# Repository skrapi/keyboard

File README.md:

# keyboard
Documenting my mechanical keyboard build

1. Put feet on case
1. Cut foam for M2 chip
1. Placed M2 Chip in keyboard
1. Plugged in computer
1. Flashing blue light on "1" key
1. Spacebar works
1. https://www.youtube.com/watch?v=usNx1_d0HbQ&t=84s
1. https://www.youtube.com/watch?v=cD5Zj-ZgMLA
1. Decided just to clip stabs, since I don't have lube
1. Mounted stabs with plastic washers
1. connected bluetooth and nfc antennas
1. Make sure that thehy are not in the way of the pcb mounting and switch connection holes
1. Cut case if needed to fit M2 boarD
1. Tested with online keyboard tester
1. Placed all the keycaps

## Designing keyboard
https://github.com/ruiqimao/keyboard-pcb-guide

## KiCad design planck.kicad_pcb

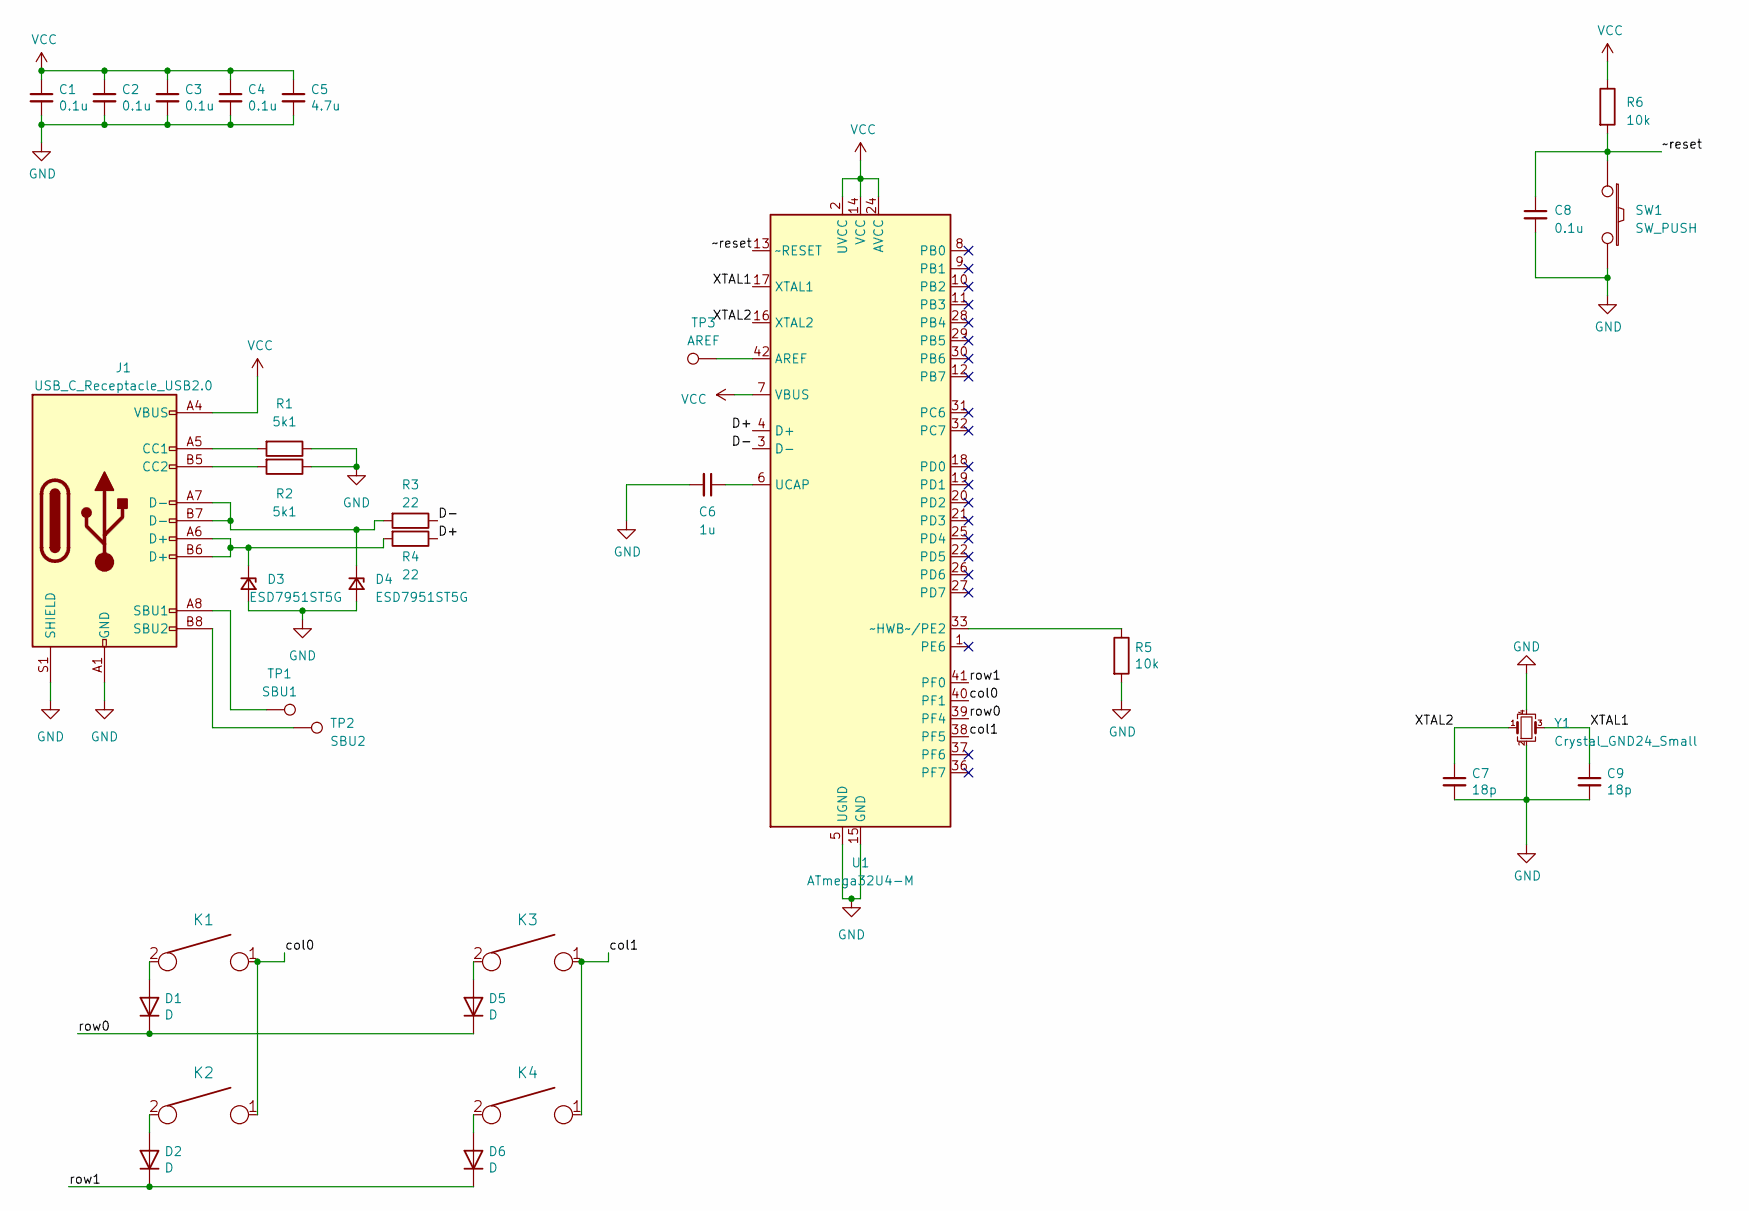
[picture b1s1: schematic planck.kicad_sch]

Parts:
C1, C2, C3, C4, C8: 0.1u; C_0402_1005Metric
C5: 4.7u; C_0402_1005Metric
C6: 1u; C_0402_1005Metric
C7, C9: 18p; C_0402_1005Metric
D1, D2, D5, D6: D; D_SOD-123
D3, D4: ESD7951ST5G; D_SOD-923
J1: USB_C_Receptacle_USB2.0; USB_C_Receptacle_Amphenol_12401610E4-2A
K1, K2, K3, K4: KEYSW; SW_Cherry_MX_1.00u_PCB
R1, R2: 5k1; R_0402_1005Metric
R3, R4: 22; R_0402_1005Metric
R5, R6: 10k; R_0402_1005Metric
SW1: SW_PUSH; SW_SPST_CK_RS282G05A3
TP1: SBU1; TestPoint_Pad_D1.0mm
TP2: SBU2; TestPoint_Pad_D1.0mm
TP3: AREF; TestPoint_Pad_D1.0mm
U1: ATmega32U4-M; QFN-44-1EP_7x7mm_P0.5mm_EP5.2x5.2mm
Y1: Crystal_GND24_Small; Crystal_SMD_SeikoEpson_FA238-4Pin_3.2x2.5mm

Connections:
/D+: R4.1, U1.4 (D+)
/D-: R3.1, U1.3 (D-)
/XTAL1: C9.1, U1.17 (XTAL1), Y1.3
/XTAL2: C7.1, U1.16 (XTAL2), Y1.1
/col0: K1.1, K2.1, U1.40 (PF1)
/col1: K3.1, K4.1, U1.38 (PF5)
/row0: D1.1 (K), D5.1 (K), U1.39 (PF4)
/row1: D2.1 (K), D6.1 (K), U1.41 (PF0)
/~reset: C8.1, R6.2, SW1.1, U1.13 (~RESET)
GND: C1.2, C2.2, C3.2, C4.2, C5.2, C6.2, C7.2, C8.2, C9.2, D3.2 (A), D4.2 (A), J1.A1 (GND), J1.A12 (GND), J1.B1 (GND), J1.B12 (GND), J1.S1 (SHIELD), R1.1, R2.1, R5.2, SW1.2, U1.5 (UGND), U1.15 (GND), U1.23 (GND), U1.35 (GND), U1.43 (GND), U1.45 (GND), Y1.2, Y1.4
unnamed: C6.1, U1.6 (UCAP)
unnamed: D1.2 (A), K1.2
unnamed: D2.2 (A), K2.2
unnamed: D3.1 (K), J1.A6 (D+), J1.B6 (D+), R4.2
unnamed: D4.1 (K), J1.A7 (D-), J1.B7 (D-), R3.2
unnamed: D5.2 (A), K3.2
unnamed: D6.2 (A), K4.2
unnamed: J1.A5 (CC1), R1.2
unnamed: J1.A8 (SBU1), TP1.1
unnamed: J1.B5 (CC2), R2.2
unnamed: J1.B8 (SBU2), TP2.1
unnamed: R5.1, U1.33 (~HWB~/PE2)
unnamed: TP3.1, U1.42 (AREF)
VCC: C1.1, C2.1, C3.1, C4.1, C5.1, J1.A4 (VBUS), J1.A9 (VBUS), J1.B4 (VBUS), J1.B9 (VBUS), R6.1, U1.2 (UVCC), U1.7 (VBUS), U1.14 (VCC), U1.24 (AVCC), U1.34 (VCC), U1.44 (AVCC)

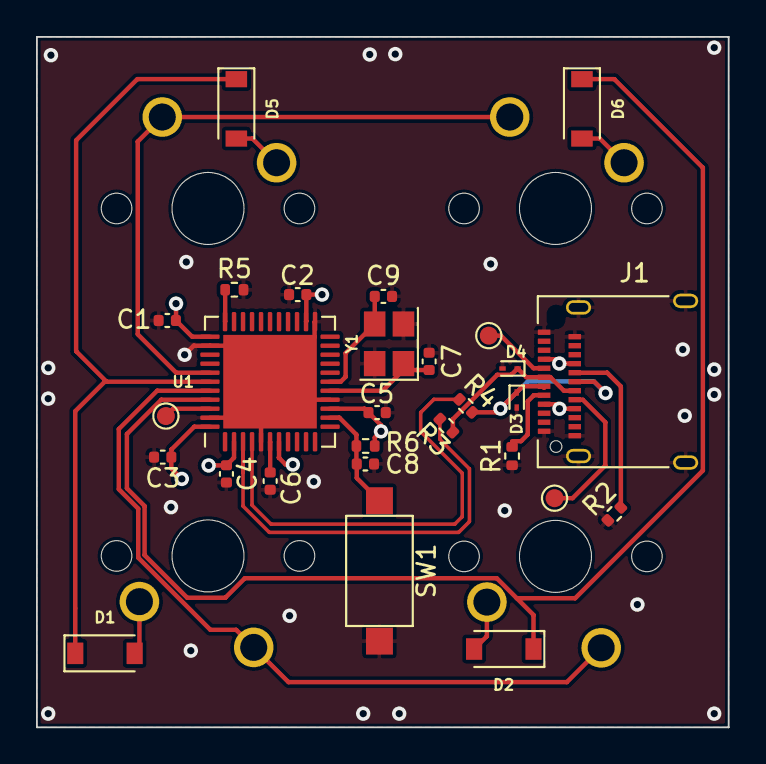
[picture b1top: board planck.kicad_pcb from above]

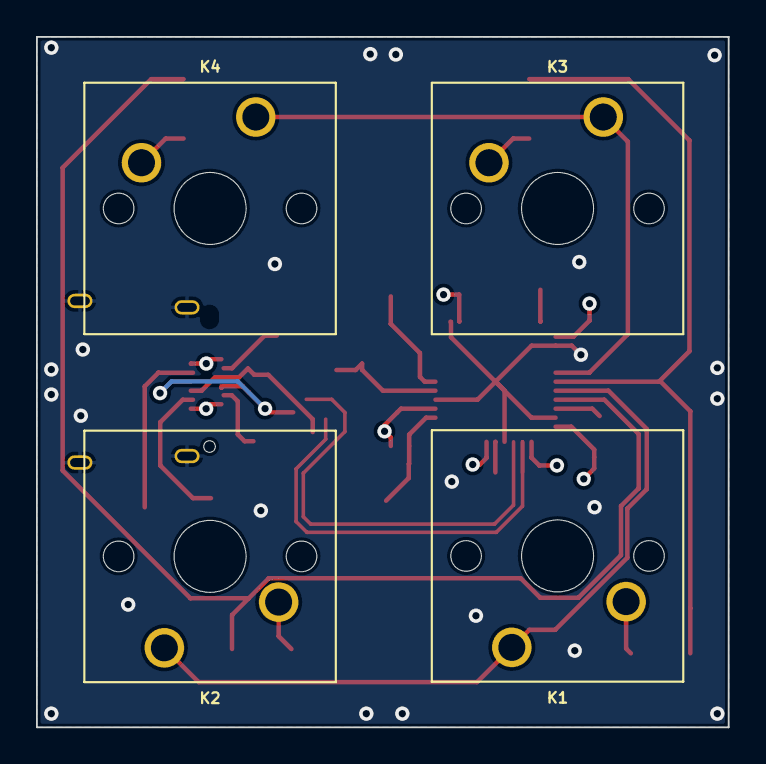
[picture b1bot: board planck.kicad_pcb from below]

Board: 4 copper layers, 38.4 x 38.4 mm, 32 parts (4 on the bottom side), 24 nets.

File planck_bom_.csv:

Component,Description,Part,References,Value,Footprint,Quantity Per PCB,Datasheet
1,"Unpolarized capacitor, small symbol",C_Small,C7 C9,18p,C_0603_1608Metric,2,~
2,"Unpolarized capacitor, small symbol",C_Small,C1 C2 C3 C4 C8,0.1u,C_0603_1608Metric,5,~
3,"Unpolarized capacitor, small symbol",C_Small,C6,1u,C_0603_1608Metric,1,~
4,"Unpolarized capacitor, small symbol",C_Small,C5,4.7u,C_0603_1608Metric,1,~
5,Diode,D,D1 D2 D5 D6,D,D_SOD-123,4,~
6,"Zener diode, small symbol",D_Zener_Small,D3 D4,ESD7951ST5G,D_SOD-923,2,~
7,USB 2.0-only Type-C Receptacle connector,USB_C_Receptacle_USB2.0,J1,USB_C_Receptacle_USB2.0,USB_C_Receptacle_Amphenol_12401548E4-2A,1,https://www.usb.org/sites/default/files/documents/usb_type-c.zip
8,,KEYSW,K1 K2 K3 K4,KEYSW,SW_Cherry_MX_1.00u_PCB,4,
9,Resistor,R,R3 R4,22,R_0603_1608Metric,2,~
10,Resistor,R,R1 R2,5k1,R_0603_1608Metric,2,~
11,Resistor,R,R5 R6,10k,R_0603_1608Metric,2,~
12,,SW_PUSH,SW1,SW_PUSH,SW_SPST_TL3342,1,
13,"16MHz, 32kB Flash, 2.5kB SRAM, 1kB EEPROM, USB 2.0, QFN-44",ATmega32U4-M,U1,ATmega32U4-M,QFN-44-1EP_7x7mm_P0.5mm_EP5.2x5.2mm,1,http://ww1.microchip.com/downloads/en/DeviceDoc/Atmel-7766-8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
14,"Four pin crystal, GND on pins 2 and 4, small symbol",Crystal_GND24_Small,Y1,Crystal_GND24_Small,Crystal_SMD_SeikoEpson_FA238-4Pin_3.2x2.5mm,1,~





Component Groups:,14
Component Count:,29
Fitted Components:,29
Number of PCBs:,1
Total components:,29
Schematic Version:,
Schematic Date:,
PCB Variant:,default
BoM Date:,Sat 10 Jul 2021 16:44:31
Schematic Source:,planck.kicad_sch
KiCad Version:,Eeschema 5.99.0-unknown-3f6811f413~130~ubuntu20.10.1

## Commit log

2021-06-09 added submodules
2021-06-10 Created schematic
2021-06-19 Upgraded to kicad 6
2021-06-19 added basic layout
2021-06-19 poured gnd plane
2021-06-19 poured fills
2021-06-19 started routing
2021-06-20 routed crystal
2021-07-04 finishing it off
2021-07-04 switched pins for switches
2021-07-04 added symbols
2021-07-04 finished layout
2021-07-11 added digikey library
2021-07-11 added new usb c
